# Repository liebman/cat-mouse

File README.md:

# Prototype Rover

Simple autonomous differential drive rover with LIDAR in RUST using an ESP32s3.

- [motor](motor) contains a simple PWM motor control for cheap brushed motors using a phase/enable type motor controller.
- [encoder](encoder) contains a PCNT based quadrature encoder controller to track the position of the encoder.
- [speed-control](speed-control) implements PID control of motor speed using encoder.
- [position-control](position-control) allows the motor position to be controlled by specifying the wanted position in degrees.
- [wheel](wheel) is an abstraction on top of position-control to specify motor position in millimeters.
- [differential-drive](differential-drive) implements rover rotation and forward/reverse movement by specifying the distance or rotation.
- [lidar](lidar) implements LIDAR with an inexpensive LD19 based Lidar like <https://www.amazon.com/dp/B0B1V8D36H>
- [rover](rover) runs around autonomously avoiding things.

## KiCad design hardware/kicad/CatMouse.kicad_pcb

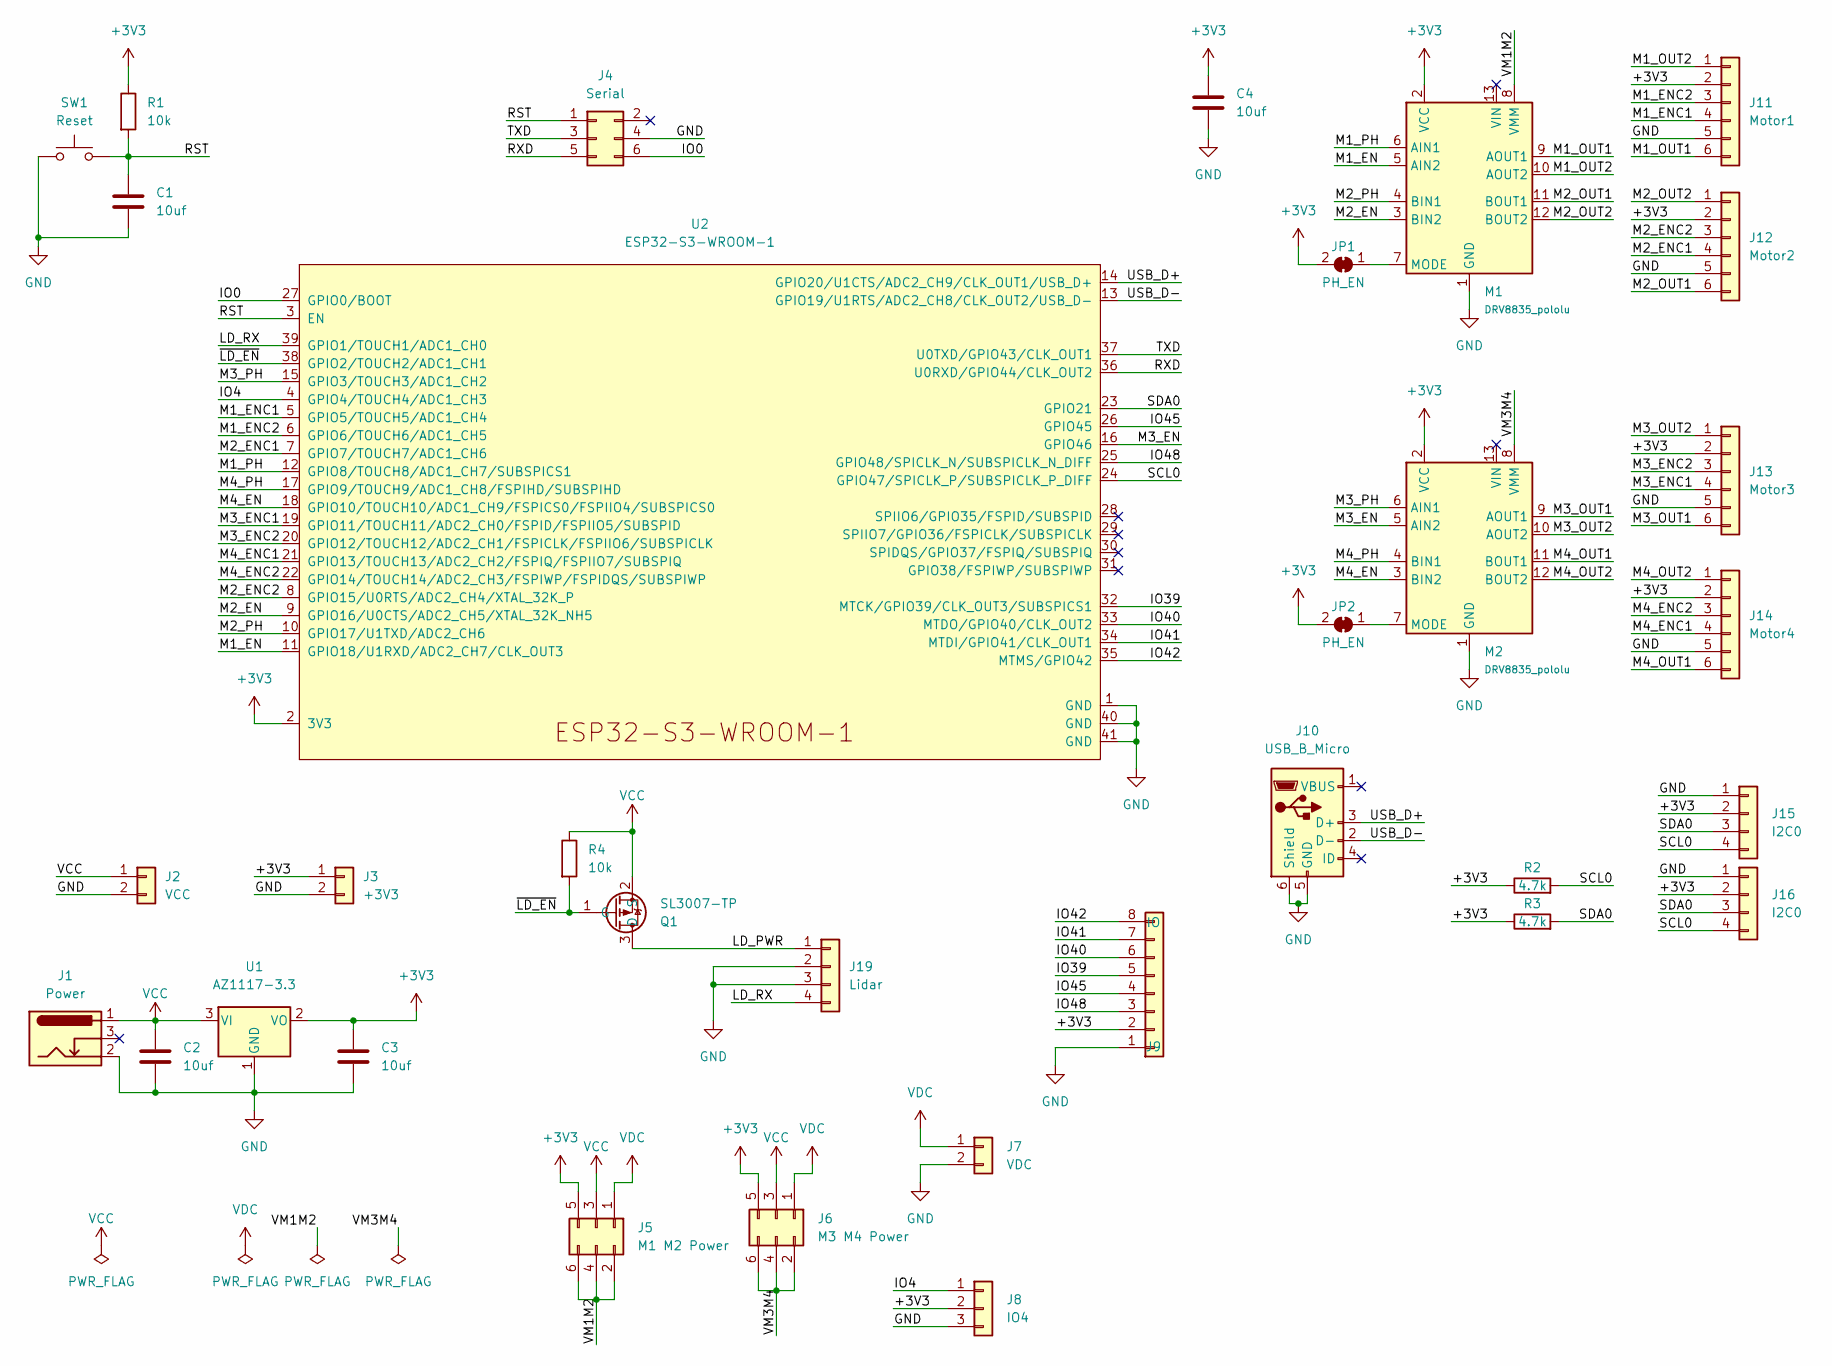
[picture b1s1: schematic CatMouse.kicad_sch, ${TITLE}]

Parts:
C1, C2, C3, C4: 10uf; C_0805_2012Metric_Pad1.18x1.45mm_HandSolder
J1: Power; BarrelJack_CUI_PJ-202A_Horizontal
J2: VCC; PinHeader_1x02_P2.54mm_Vertical
J3: +3V3; PinHeader_1x02_P2.54mm_Vertical
J4: Serial; IDC-Header_2x03_P2.54mm_Vertical
J5: M1 M2 Power; PinHeader_2x03_P2.54mm_Vertical
J6: M3 M4 Power; PinHeader_2x03_P2.54mm_Vertical
J7: VDC; PinHeader_1x02_P2.54mm_Vertical
J8: IO4; PinHeader_1x03_P2.54mm_Vertical
J9: IO; PinHeader_1x08_P2.54mm_Vertical
J10: USB_B_Micro; USB_Micro-B_GCT_USB3076-30-A
J11: Motor1; JST_ZH_B6B-ZR_1x06_P1.50mm_Vertical
J12: Motor2; JST_ZH_B6B-ZR_1x06_P1.50mm_Vertical
J13: Motor3; JST_ZH_B6B-ZR_1x06_P1.50mm_Vertical
J14: Motor4; JST_ZH_B6B-ZR_1x06_P1.50mm_Vertical
J15, J16: I2C0; PinHeader_1x04_P2.54mm_Vertical
J19: Lidar; JST_ZH_B4B-ZR_1x04_P1.50mm_Vertical
JP1, JP2: PH_EN; SolderJumper-2_P1.3mm_Bridged_RoundedPad1.0x1.5mm
M1, M2: DRV8835_pololu
Q1: SL3007-TP; SOT-23
R1, R4: 10k; R_0805_2012Metric_Pad1.20x1.40mm_HandSolder
R2, R3: 4.7k; R_0805_2012Metric_Pad1.20x1.40mm_HandSolder
SW1: Reset; SW_PUSH_6mm
U1: AZ1117-3.3; SOT-223-3_TabPin2
U2: ESP32-S3-WROOM-1

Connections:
+3V3: C3.1, C4.1, J3.1, J5.5, J6.5, J8.2, J9.2, J11.2, J12.2, J13.2, J14.2, J15.2, J16.2, JP1.2 (B), JP2.2 (B), M1.2 (VCC), M2.2 (VCC), R1.1, R2.1, R3.1, U1.2 (VO), U2.2 (3V3)
/IO0: J4.6, U2.27 (GPIO0/BOOT)
/IO4: J8.1, U2.4 (GPIO4/TOUCH4/ADC1_CH3)
/IO39: J9.5, U2.32 (MTCK/GPIO39/CLK_OUT3/SUBSPICS1)
/IO40: J9.6, U2.33 (MTDO/GPIO40/CLK_OUT2)
/IO41: J9.7, U2.34 (MTDI/GPIO41/CLK_OUT1)
/IO42: J9.8, U2.35 (MTMS/GPIO42)
/IO45: J9.4, U2.26 (GPIO45)
/IO48: J9.3, U2.25 (GPIO48/SPICLK_N/SUBSPICLK_N_DIFF)
/LD_PWR: J19.1, Q1.3 (D)
/LD_RX: J19.4, U2.39 (GPIO1/TOUCH1/ADC1_CH0)
/M1_EN: M1.5 (AIN2), U2.11 (GPIO18/U1RXD/ADC2_CH7/CLK_OUT3)
/M1_ENC1: J11.4, U2.5 (GPIO5/TOUCH5/ADC1_CH4)
/M1_ENC2: J11.3, U2.6 (GPIO6/TOUCH6/ADC1_CH5)
/M1_OUT1: J11.6, M1.9 (AOUT1)
/M1_OUT2: J11.1, M1.10 (AOUT2)
/M1_PH: M1.6 (AIN1), U2.12 (GPIO8/TOUCH8/ADC1_CH7/SUBSPICS1)
/M2_EN: M1.3 (BIN2), U2.9 (GPIO16/U0CTS/ADC2_CH5/XTAL_32K_NH5)
/M2_ENC1: J12.4, U2.7 (GPIO7/TOUCH7/ADC1_CH6)
/M2_ENC2: J12.3, U2.8 (GPIO15/U0RTS/ADC2_CH4/XTAL_32K_P)
/M2_OUT1: J12.6, M1.11 (BOUT1)
/M2_OUT2: J12.1, M1.12 (BOUT2)
/M2_PH: M1.4 (BIN1), U2.10 (GPIO17/U1TXD/ADC2_CH6)
/M3_EN: M2.5 (AIN2), U2.16 (GPIO46)
/M3_ENC1: J13.4, U2.19 (GPIO11/TOUCH11/ADC2_CH0/FSPID/FSPIIO5/S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)
/M3_ENC2: J13.3, U2.20 (GPIO12/TOUCH12/ADC2_CH1/FSPICLK/FSPIIO6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)
/M3_OUT1: J13.6, M2.9 (AOUT1)
/M3_OUT2: J13.1, M2.10 (AOUT2)
/M3_PH: M2.6 (AIN1), U2.15 (GPIO3/TOUCH3/ADC1_CH2)
/M4_EN: M2.3 (BIN2), U2.18 (GPIO10/TOUCH10/ADC1_CH9/FSPICS0/FSPIIO4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)
/M4_ENC1: J14.4, U2.21 (GPIO13/TOUCH13/ADC2_CH2/FSPIQ/FSPIIO7/S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)
/M4_ENC2: J14.3, U2.22 (GPIO14/TOUCH14/ADC2_CH3/FSPIWP/FSPIDQS/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)
/M4_OUT1: J14.6, M2.11 (BOUT1)
/M4_OUT2: J14.1, M2.12 (BOUT2)
/M4_PH: M2.4 (BIN1), U2.17 (GPIO9/TOUCH9/ADC1_CH8/FSPIHD/SUBSPIHD)
/RST: C1.1, J4.1, R1.2, SW1.2, U2.3 (EN)
/RXD: J4.5, U2.36 (U0RXD/GPIO44/CLK_OUT2)
/SCL0: J15.4, J16.4, R2.2, U2.24 (GPIO47/SPICLK_P/SUBSPICLK_P_DIFF)
/SDA0: J15.3, J16.3, R3.2, U2.23 (GPIO21)
/TXD: J4.3, U2.37 (U0TXD/GPIO43/CLK_OUT1)
/USB_D+: J10.3 (D+), U2.14 (GPIO20/U1CTS/ADC2_CH9/CLK_OUT1/USB_D+)
/USB_D-: J10.2 (D-), U2.13 (GPIO19/U1RTS/ADC2_CH8/CLK_OUT2/USB_D-)
/VM1M2: J5.2, J5.4, J5.6, M1.8 (VMM)
/VM3M4: J6.2, J6.4, J6.6, M2.8 (VMM)
/~LD_EN: Q1.1 (G), R4.2, U2.38 (GPIO2/TOUCH2/ADC1_CH1)
GND: C1.2, C2.2, C3.2, C4.2, J1.2, J2.2, J3.2, J4.4, J7.2, J8.3, J9.1, J10.5 (GND), J10.6 (Shield), J11.5, J12.5, J13.5, J14.5, J15.1, J16.1, J19.2, J19.3, M1.1 (GND), M1.14 (GND), M2.1 (GND), M2.14 (GND), SW1.1, U1.1 (GND), U2.1 (GND), U2.40 (GND), U2.41 (GND)
unnamed: JP1.1 (A), M1.7 (MODE)
unnamed: JP2.1 (A), M2.7 (MODE)
VCC: C2.1, J1.1, J2.1, J5.3, J6.3, Q1.2 (S), R4.1, U1.3 (VI)
VDC: J5.1, J6.1, J7.1

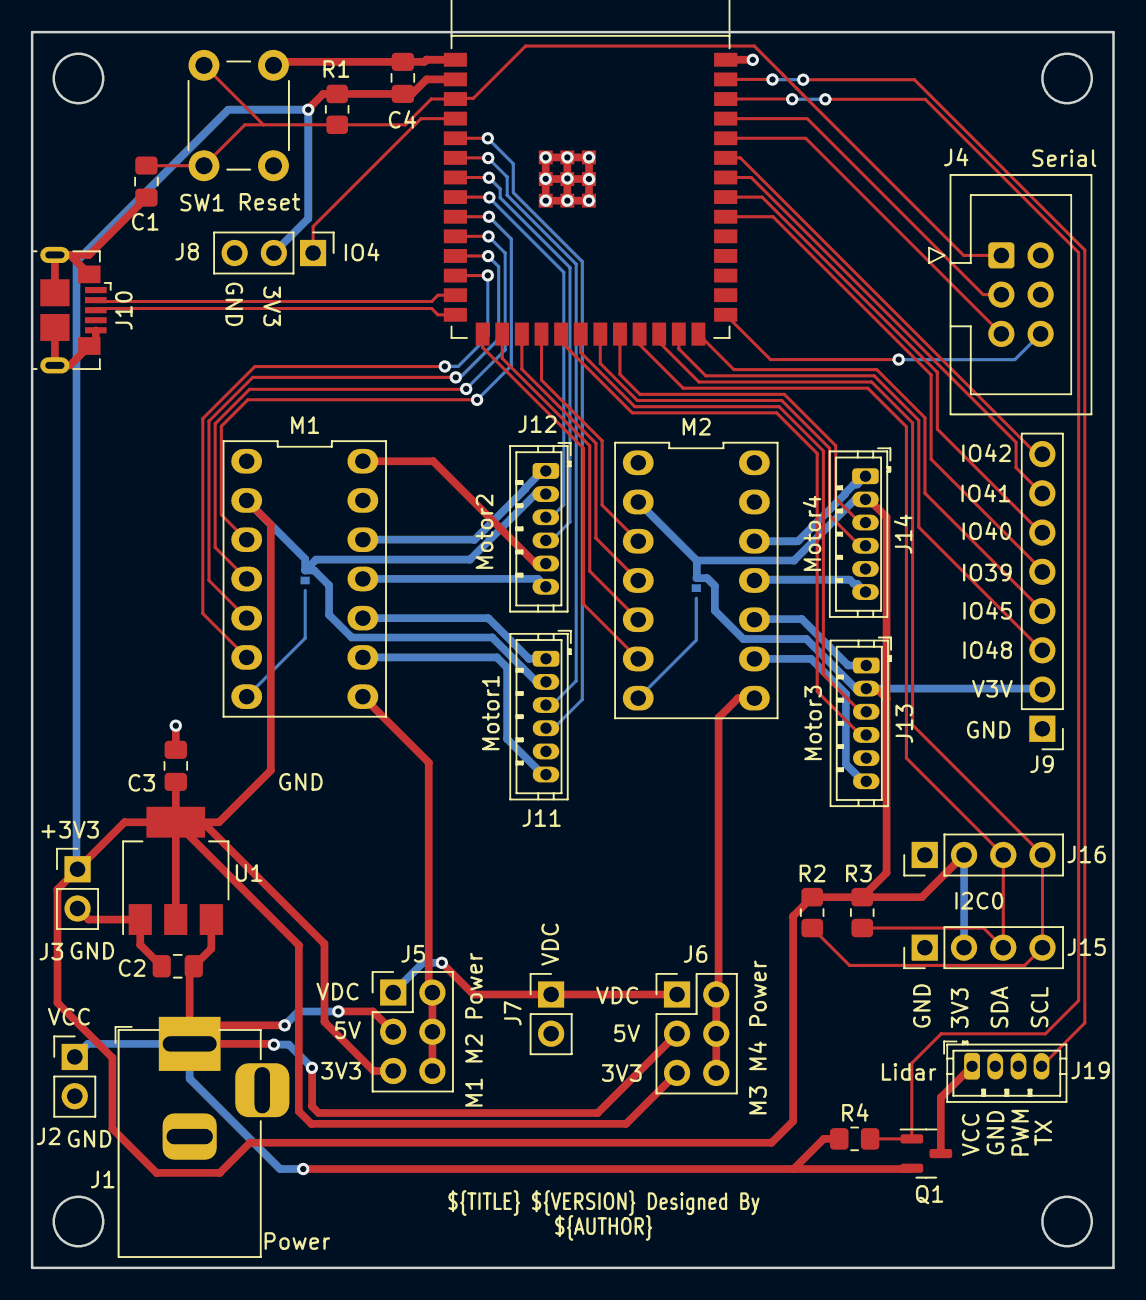
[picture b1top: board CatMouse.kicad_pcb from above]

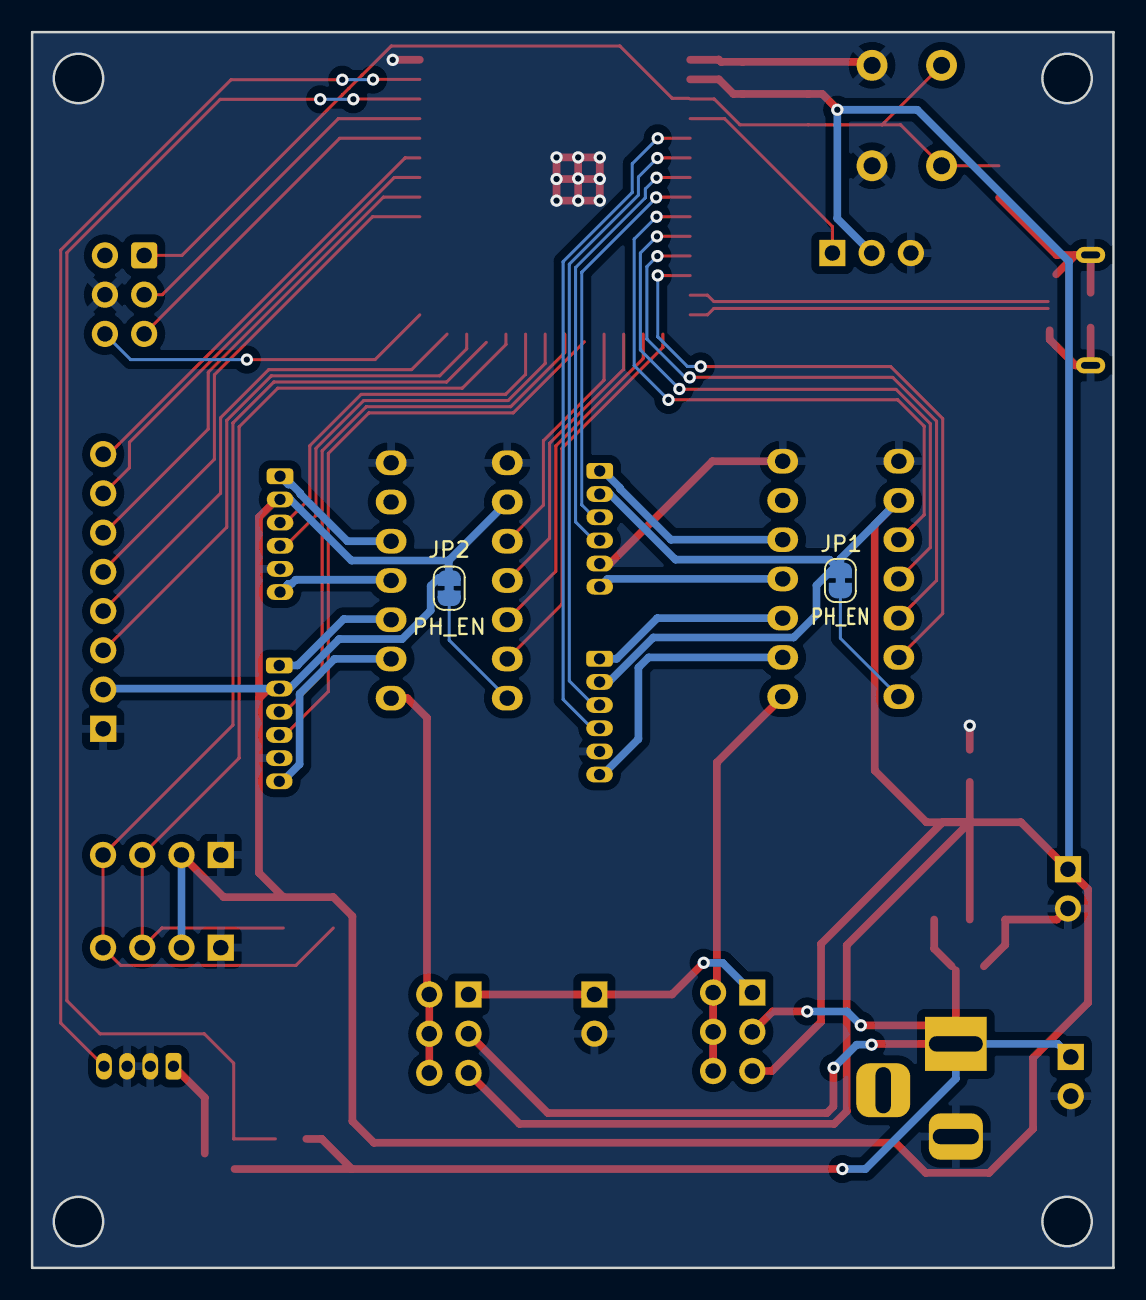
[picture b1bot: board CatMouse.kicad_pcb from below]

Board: 2 copper layers, 70.0 x 80.0 mm, 33 parts (2 on the bottom side), 50 nets.

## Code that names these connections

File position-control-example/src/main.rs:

use std::time::Duration;

use anyhow::Context;
use embedded_hal::delay::DelayUs;
use esp_idf_hal::delay::FreeRtos as delay;
use esp_idf_hal::ledc::config;
use esp_idf_hal::ledc::LedcTimerDriver;
use esp_idf_hal::ledc::Resolution;
use esp_idf_hal::prelude::*;
use log::*;

use encoder::Encoder;
use motor::Motor;
use position_control::PositionControl;
use position_control::PositionControlCmd;
use speed_control::SpeedControl;

const TICKS_PER_REVOLUTION: u32 = 1440;

const SPEED_CONFIG: speed_control::Config = speed_control::Config {
    interval: Duration::from_millis(100),
    p: 0.5,
    i: 0.1,
    d: 0.2,
};

const POSITION_CONFIG: position_control::Config = position_control::Config {
    interval: Duration::from_millis(100),
    p: 0.5,
    i: 0.01,
    d: 0.2,
};

fn main() -> anyhow::Result<()> {
    esp_idf_sys::link_patches();
    // Bind the log crate to the ESP Logging facilities
    esp_idf_svc::log::EspLogger::initialize_default();
    info!("starting");
    let peripherals = Peripherals::take().context("failed to take Peripherals")?;
    // left motor pins
    let pin_m1_ph = peripherals.pins.gpio8;
    let pin_m1_en = peripherals.pins.gpio18;
    // right motor pins
    let pin_m2_ph = peripherals.pins.gpio17;
    let pin_m2_en = peripherals.pins.gpio16;
    // left encoder pins
    let pin_m1_enc1 = peripherals.pins.gpio5;
    let pin_m1_enc2 = peripherals.pins.gpio6;
    // right encoder pins
    let pin_m2_enc1 = peripherals.pins.gpio7;
    let pin_m2_enc2 = peripherals.pins.gpio15;

    let config = config::TimerConfig::new()
        .frequency(50.Hz())
        .resolution(Resolution::Bits10);
    let timer_driver =
        LedcTimerDriver::new(peripherals.ledc.timer0, &config).context("creating timer driver")?;

    let motor_left = Motor::new(
        "left",
        peripherals.ledc.channel0,
        &timer_driver,
        pin_m1_ph,
        pin_m1_en,
        false,
    )
    .context("creating left motor")?;

    let motor_right = Motor::new(
        "right",
        peripherals.ledc.channel1,
        &timer_driver,
        pin_m2_ph,
        pin_m2_en,
        true,
    )
    .context("creating right motor")?;

    let encoder_left = Encoder::new(
        peripherals.pcnt0,
        pin_m1_enc1,
        pin_m1_enc2,
        TICKS_PER_REVOLUTION,
        false,
    )
    .context("create left encoder")?;

    let encoder_right = Encoder::new(
        peripherals.pcnt1,
        pin_m2_enc1,
        pin_m2_enc2,
        TICKS_PER_REVOLUTION,
        true,
    )
    .context("create right encoder")?;

    let speed_left = SpeedControl::new(motor_left, encoder_left, SPEED_CONFIG)?;
    let speed_right = SpeedControl::new(motor_right, encoder_right, SPEED_CONFIG)?;

    let position_left = PositionControl::new(speed_left, POSITION_CONFIG, 720.0)?;
    let position_right = PositionControl::new(speed_right, POSITION_CONFIG, 720.0)?;

    let mut reporter = PositinReporter::new();

    info!("forward");
    position_left.send(PositionControlCmd::SetPosition(10000))?;
    position_right.send(PositionControlCmd::SetPosition(10000))?;
    while position_left.is_active() && position_right.is_active() {
        reporter.update(position_left.get_position(), position_right.get_position());
        delay.delay_ms(1000);
    }
    info!("done");
    delay.delay_ms(1000);
    info!("reverse");
    position_left.send(PositionControlCmd::SetPosition(0))?;
    position_right.send(PositionControlCmd::SetPosition(0))?;
    while position_left.is_active() && position_right.is_active() {
        reporter.update(position_left.get_position(), position_right.get_position());
        delay.delay_ms(1000);
    }
    info!("done");

    loop {
        delay.delay_ms(1000);
    }
}

#[derive(Debug)]
struct PositinReporter {
    left: i64,
    right: i64,
}

impl PositinReporter {
    fn new() -> Self {
        Self { left: 0, right: 0 }
    }

    fn update(&mut self, left: i64, right: i64) -> bool {
        if (left, right) != (self.left, self.right) {
            (self.left, self.right) = (left, right);
            info!("{self:+?}");
            return true;
        }
        false
    }
}

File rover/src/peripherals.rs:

use esp_idf_hal::gpio::AnyIOPin;
use esp_idf_hal::gpio::AnyInputPin;
use esp_idf_hal::gpio::AnyOutputPin;
use esp_idf_hal::i2c::I2C0;
use esp_idf_hal::ledc::CHANNEL0;
use esp_idf_hal::ledc::CHANNEL1;
use esp_idf_hal::ledc::TIMER0;
use esp_idf_hal::modem::Modem;
use esp_idf_hal::pcnt::PCNT0;
use esp_idf_hal::pcnt::PCNT1;
use esp_idf_hal::prelude::Peripherals;
use esp_idf_hal::uart::UART1;

pub struct SystemPeripherals<C0, C1, T, I, P0, P1, U> {
    pub i2c_unit: I,
    pub i2c_pins: I2cPeripherals,
    pub ledc_timer: T,
    pub left_motor: MotorPeripherals<C0>,
    pub left_encoder: EncoderPeripherals<P0>,
    pub right_motor: MotorPeripherals<C1>,
    pub right_encoder: EncoderPeripherals<P1>,
    pub lidar: LidarPeripherals<U>,
    pub modem: Modem,
}

impl SystemPeripherals<CHANNEL0, CHANNEL1, TIMER0, I2C0, PCNT0, PCNT1, UART1> {
    pub fn take() -> Self {
        let peripherals = Peripherals::take().unwrap();

        Self {
            i2c_unit: peripherals.i2c0,
            i2c_pins: I2cPeripherals {
                sda: peripherals.pins.gpio21.into(),
                scl: peripherals.pins.gpio47.into(),
            },
            ledc_timer: peripherals.ledc.timer0,
            left_motor: MotorPeripherals {
                channel: peripherals.ledc.channel0,
                ph: peripherals.pins.gpio8.into(),
                en: peripherals.pins.gpio18.into(),
            },
            left_encoder: EncoderPeripherals {
                pcnt: peripherals.pcnt0,
                a: peripherals.pins.gpio5.into(),
                b: peripherals.pins.gpio6.into(),
            },
            right_motor: MotorPeripherals {
                channel: peripherals.ledc.channel1,
                ph: peripherals.pins.gpio17.into(),
                en: peripherals.pins.gpio16.into(),
            },
            right_encoder: EncoderPeripherals {
                pcnt: peripherals.pcnt1,
                a: peripherals.pins.gpio7.into(),
                b: peripherals.pins.gpio15.into(),
            },
            lidar: LidarPeripherals {
                uart: peripherals.uart1,
                serial: peripherals.pins.gpio1.into(),
                power: peripherals.pins.gpio2.into(),
            },
            modem: peripherals.modem,
        }
    }
}

pub struct MotorPeripherals<C> {
    pub channel: C,
    pub ph: AnyOutputPin,
    pub en: AnyOutputPin,
}

pub struct EncoderPeripherals<P> {
    pub pcnt: P,
    pub a: AnyInputPin,
    pub b: AnyInputPin,
}

pub struct LidarPeripherals<U> {
    pub uart: U,
    pub serial: AnyInputPin,
    pub power: AnyOutputPin,
}

pub struct I2cPeripherals {
    pub sda: AnyIOPin,
    pub scl: AnyIOPin,
}

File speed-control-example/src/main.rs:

use std::time::Duration;

use esp_idf_hal::delay::FreeRtos as delay;
use esp_idf_hal::ledc::config;
use esp_idf_hal::ledc::LedcTimerDriver;
use esp_idf_hal::ledc::Resolution;
use esp_idf_hal::prelude::*;

use anyhow::Context;
use embedded_hal::delay::DelayUs;
use log::*;

use encoder::Encoder;
use motor::Motor;
use speed_control::SpeedControl;
use speed_control::SpeedControlCmd;

const TICKS_PER_REVOLUTION: u32 = 1440;

const LIDAR_CONFIG: speed_control::Config = speed_control::Config {
    interval: Duration::from_millis(100),
    p: 0.5,
    i: 0.1,
    d: 0.2,
};

fn main() -> anyhow::Result<()> {
    esp_idf_sys::link_patches();
    // Bind the log crate to the ESP Logging facilities
    esp_idf_svc::log::EspLogger::initialize_default();
    info!("starting");
    let peripherals = Peripherals::take().context("failed to take Peripherals")?;
    // lidar motor pins
    let pin_m3_en = peripherals.pins.gpio46;
    let pin_m3_ph = peripherals.pins.gpio3;
    // lidar encoder pins
    let pin_m3_enc1 = peripherals.pins.gpio11;
    let pin_m3_enc2 = peripherals.pins.gpio12;

    let config = config::TimerConfig::new()
        .frequency(50.Hz())
        .resolution(Resolution::Bits10);
    let timer_driver =
        LedcTimerDriver::new(peripherals.ledc.timer0, &config).context("creating timer driver")?;

    let motor_lidar = Motor::new(
        "lidar",
        peripherals.ledc.channel0,
        &timer_driver,
        pin_m3_ph,
        pin_m3_en,
        true,
    )
    .context("creating lidar motor")?;

    let encoder_lidar = Encoder::new(
        peripherals.pcnt0,
        pin_m3_enc1,
        pin_m3_enc2,
        TICKS_PER_REVOLUTION,
        true,
    )
    .context("create lidar encoder")?;

    let lidar = SpeedControl::new(motor_lidar, encoder_lidar, LIDAR_CONFIG)?;
    lidar.send(SpeedControlCmd::SetSpeed(360.0))?;

    loop {
        delay.delay_ms(1000);
    }
}

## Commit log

2023-06-24 initial commit / functional rover
2023-06-24 add picture
2023-06-24 added schematic to readme
2023-06-24 added MIT license
2023-06-30 board v0.4
2023-06-30 real 0.4
2023-07-05 board 0.5 & fusion360 & stl files
2023-07-08 functional with new lidar
2023-07-08 update readme (still need to update schematic and image)
2023-07-08 cargo fmt
2023-07-08 update schematic
2023-07-09 update to current git (unreleased) esp-idf-{sys,hal,svc}
2023-07-14 update for new boards (v0.5)
2023-07-14 add left/right motor control to brain/http controler for testing
2023-07-15 tune Moving side distances
